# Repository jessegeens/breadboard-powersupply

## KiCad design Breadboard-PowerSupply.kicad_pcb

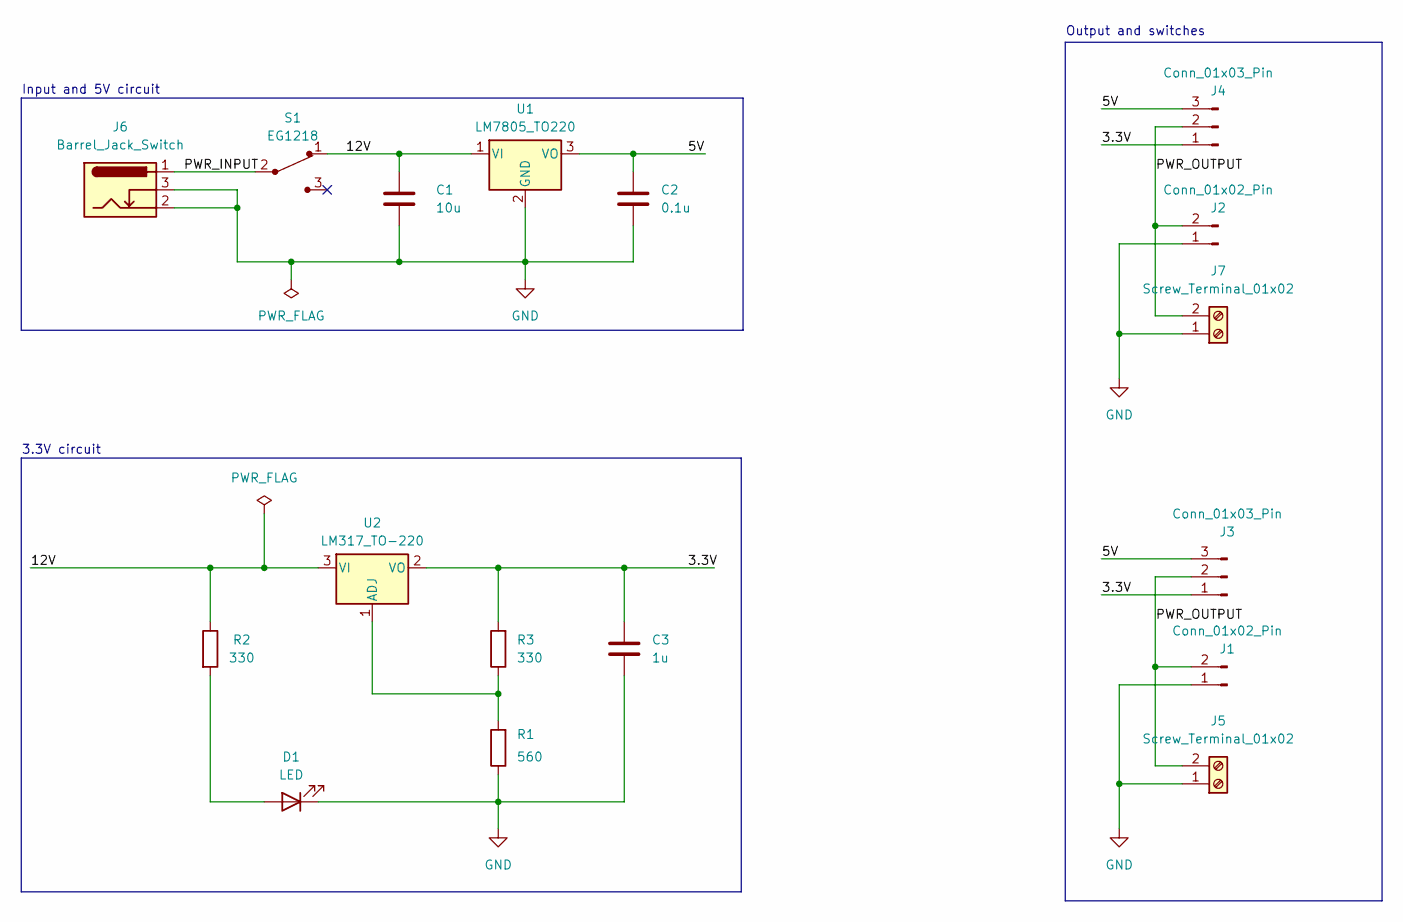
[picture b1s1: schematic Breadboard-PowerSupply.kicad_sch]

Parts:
C1: 10u; C_Disc_D3.0mm_W1.6mm_P2.50mm
C2: 0.1u; C_Disc_D3.0mm_W1.6mm_P2.50mm
C3: 1u; C_Disc_D3.0mm_W1.6mm_P2.50mm
D1: LED; LED_D5.0mm
J1, J2: Conn_01x02_Pin; PinHeader_1x02_P2.54mm_Vertical
J3, J4: Conn_01x03_Pin; PinHeader_1x03_P2.54mm_Vertical
J5, J7: Screw_Terminal_01x02; TerminalBlock_bornier-2_P5.08mm
J6: Barrel_Jack_Switch; BarrelJack_Horizontal
R1: 560; R_Axial_DIN0204_L3.6mm_D1.6mm_P7.62mm_Horizontal
R2, R3: 330; R_Axial_DIN0204_L3.6mm_D1.6mm_P7.62mm_Horizontal
S1: EG1218; Switch_Slide_11.6x4mm_EG1218; MPN EG1218; Digi-Key_PN EG1903-ND
U1: LM7805_TO220; TO-220-3_Vertical
U2: LM317_TO-220; TO-220-3_Vertical

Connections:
/3.3V: C3.1, J3.1, J4.1, R3.2, U2.2 (VO)
/5V: C2.1, J3.3, J4.3, U1.3 (VO)
/12V: C1.1, R2.1, S1.1, U1.1 (VI), U2.3 (VI)
/PWR_INPUT: J6.1, S1.2
/PWR_OUTPUT: J1.2, J2.2, J3.2, J4.2, J5.2, J7.2
GND: C1.2, C2.2, C3.2, D1.1 (K), J1.1, J2.1, J5.1, J6.2, J6.3, J7.1, R1.1, U1.2 (GND)
unnamed: D1.2 (A), R2.2
unnamed: R1.2, R3.1, U2.1 (ADJ)

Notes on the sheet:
Output and switches
3.3V circuit
Input and 5V circuit

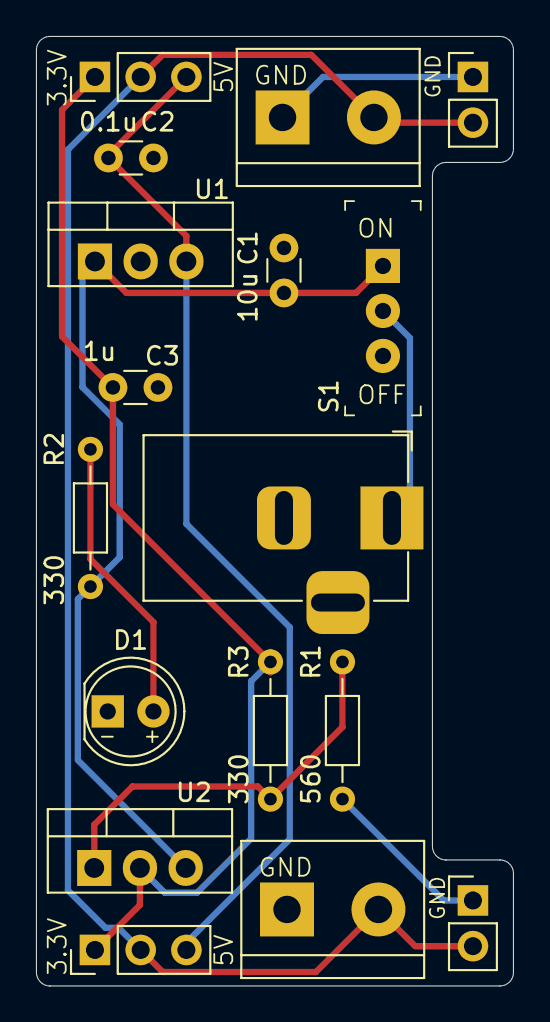
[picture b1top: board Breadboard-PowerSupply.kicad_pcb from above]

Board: 2 copper layers, 26.5 x 52.8 mm, 17 parts (0 on the bottom side), 8 nets.

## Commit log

2025-06-09 v0.1
